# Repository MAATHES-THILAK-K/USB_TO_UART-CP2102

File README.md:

# USB_TO_UART-CP2102

This is a simple and compact USB to UART (serial) converter board designed using the **CP2102 IC** from **Silicon Labs**, with a USB-C input interface. The board was created in **KiCad** and is suitable for use in embedded system development, serial debugging, or programming microcontrollers like STM32, ESP32, Arduino, and more.

## 🔍 About the CP2102

The **CP2102** is a popular single-chip USB to UART bridge manufactured by **Silicon Labs**. It integrates a USB 2.0 transceiver, a crystal-less oscillator, EEPROM, and UART logic in one compact package, making it ideal for simple, low-cost serial communication with PCs or other USB hosts.

### 💡 Where It's Commonly Used

- USB serial debug tools
- Microcontroller bootloader interfaces
- Firmware flashing tools for ESP8266 / ESP32
- Industrial sensor-to-PC interfaces
- USB-based serial consoles (Linux serial TTY access)

---

## 🔗 Features

- USB to UART bridge using **CP2102**
- USB-C connector for modern device compatibility
- 0603 SMD components for compact layout
- Designed using KiCad 6+
- Gerbers ready for fabrication

---

| File/Folder  | Description                                                                 |
| ------------ | --------------------------------------------------------------------------- |
| `.kicad_pro` | KiCad project file (project configuration)                                  |
| `.kicad_sch` | Schematic file (circuit design)                                             |
| `.kicad_pcb` | PCB layout file (2D + 3D design of the board)                               |
| `gerbers/`   | Folder containing Gerber files and drill data for PCB fabrication           |
| `.step`      | 3D model of the assembled PCB for enclosure design and mechanical CAD usage |

---

## ⚙️ Comparison with Other USB-to-UART Chips

| Chip        | Manufacturer   | Max Baud Rate | Supply Voltage | Notes |
|-------------|----------------|---------------|----------------|-------|
| **CP2102**  | Silicon Labs   | ~1 Mbps       | 3.3V or 5V     | Reliable, widely supported               |
| CH340G      | WCH (China)    | ~921.6 kbps   | 5V             | Cheap, needs driver on Windows           |
| FT232RL     | FTDI           | ~3 Mbps       | 3.3V / 5V      | Expensive but robust and driver-friendly |
| PL2303      | Prolific       | ~1 Mbps       | 3.3V / 5V      | Less reliable in some OS versions        |

> 💬 The **CP2102** offers a good balance of **cost, stability, and driver support** (native support in Windows, Linux, macOS). It is more stable than CH340G, and more affordable than FT232RL.

---

## 🏗️ Applications

- Serial console access for Linux/Raspberry Pi
- Programming ESP8266/ESP32 boards
- USB-based microcontroller bootloader communication
- Debugging UART output of embedded systems

---

## 📌 Notes

- TX, RX, GND, 3.3V/5V, and DTR/RTS signals can be broken out depending on layout.
- USB-C connector provides better mechanical strength than micro-USB.
- LDO regulator is optional; useful if powering external 3.3V peripherals.

---

## 📤 License

This hardware design is open source and released under the **MIT License**. You are free to use, modify, and distribute it.

---

## 🖼️ Preview

3d Images are added with FRONT,BACK,and ISOMETRIC views.

---
🔗 GrabCAD Model (3D STEP File)

Check out the 3D model of this project on my GrabCAD profile:
👉 https://grabcad.com/maathes.thilak-1

You can view, download, and integrate the .STEP file for enclosure development or CAD simulation.

---

## 🤝 Contributions

Feel free to fork, improve, or suggest enhancements via pull requests or issues!

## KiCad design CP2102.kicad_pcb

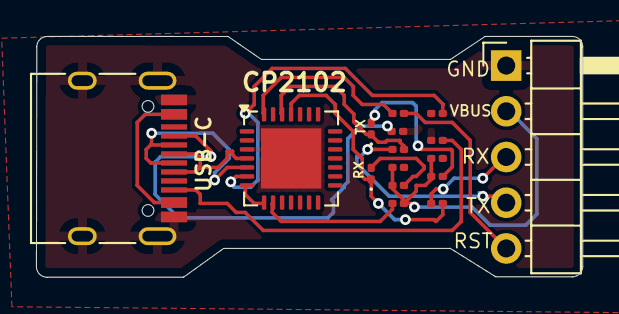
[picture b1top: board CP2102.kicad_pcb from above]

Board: 2 copper layers, 30.3 x 13.4 mm, 16 parts (0 on the bottom side), 17 nets.

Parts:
C1, C2, C3, C4: 100nf; C_0201_0603Metric
D4, D5: LED; LED_0201_0603Metric
J1: USB_C_Receptacle_USB2.0_16P; USB_C_Receptacle_HRO_TYPE-C-31-M-12
J2: Conn_01x05_Pin; PinHeader_1x05_P2.54mm_Horizontal
R1, R2: 5.1k; R_0201_0603Metric
R3: 10k; R_0201_0603Metric
R4, R5, R6, R7: 1k; R_0201_0603Metric
U1: CP2102N-Axx-xQFN28; QFN-28-1EP_5x5mm_P0.5mm_EP3.35x3.35mm

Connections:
/D+: J1.A6 (D+), J1.B6 (D+), U1.4 (D+)
/D-: J1.A7 (D-), J1.B7 (D-), U1.5 (D-)
/RST: C2.2, J2.5
/RX: J2.3, R5.1
/TX: J2.4, R4.1
/VBUS: C3.1, C4.1, J2.2, R3.1, R6.1, R7.1, U1.7 (VREGIN), U1.8 (VBUS)
GND: C1.1, C3.2, C4.2, J1.A1 (GND), J1.A12 (GND), J1.B1 (GND), J1.B12 (GND), J1.S1 (SHIELD), J2.1, R1.2, R2.1, U1.3 (GND), U1.29 (GND)
unnamed: J1.A4 (VBUS), J1.A9 (VBUS), J1.B4 (VBUS), J1.B9 (VBUS)
unnamed: D4.2 (A), R6.2
unnamed: D4.1 (K), R4.2, U1.26 (TXD)
unnamed: D5.2 (A), R7.2
unnamed: D5.1 (K), R5.2, U1.25 (RXD)
unnamed: J1.A5 (CC1), R1.1
unnamed: J1.B5 (CC2), R2.2
unnamed: C1.2, U1.6 (VDD)
unnamed: C2.1, U1.28 (~DTR)
unnamed: R3.2, U1.9 (~RST)

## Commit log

2025-06-23 Gerber files for the CP2120 USB TO UART Uploaded
2025-06-23 Uploaded the 3d View of the PCB
2025-06-23 3D model for CP2102 was added - STEP file
2025-12-27 Create temp
